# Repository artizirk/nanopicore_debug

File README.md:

# NanoPI NEO Core Debug shield

This shield provides one USB A and a uart0 via ch340 chip on seperate Micro USB connector

### Armbian Device Tree overlay for power off button on GPIO PL11

gpio-button.dts file contains the overlay. Follow [Armbian docs] to apply it.

[Armbian docs]: https://docs.armbian.com/User-Guide_Allwinner_overlays/

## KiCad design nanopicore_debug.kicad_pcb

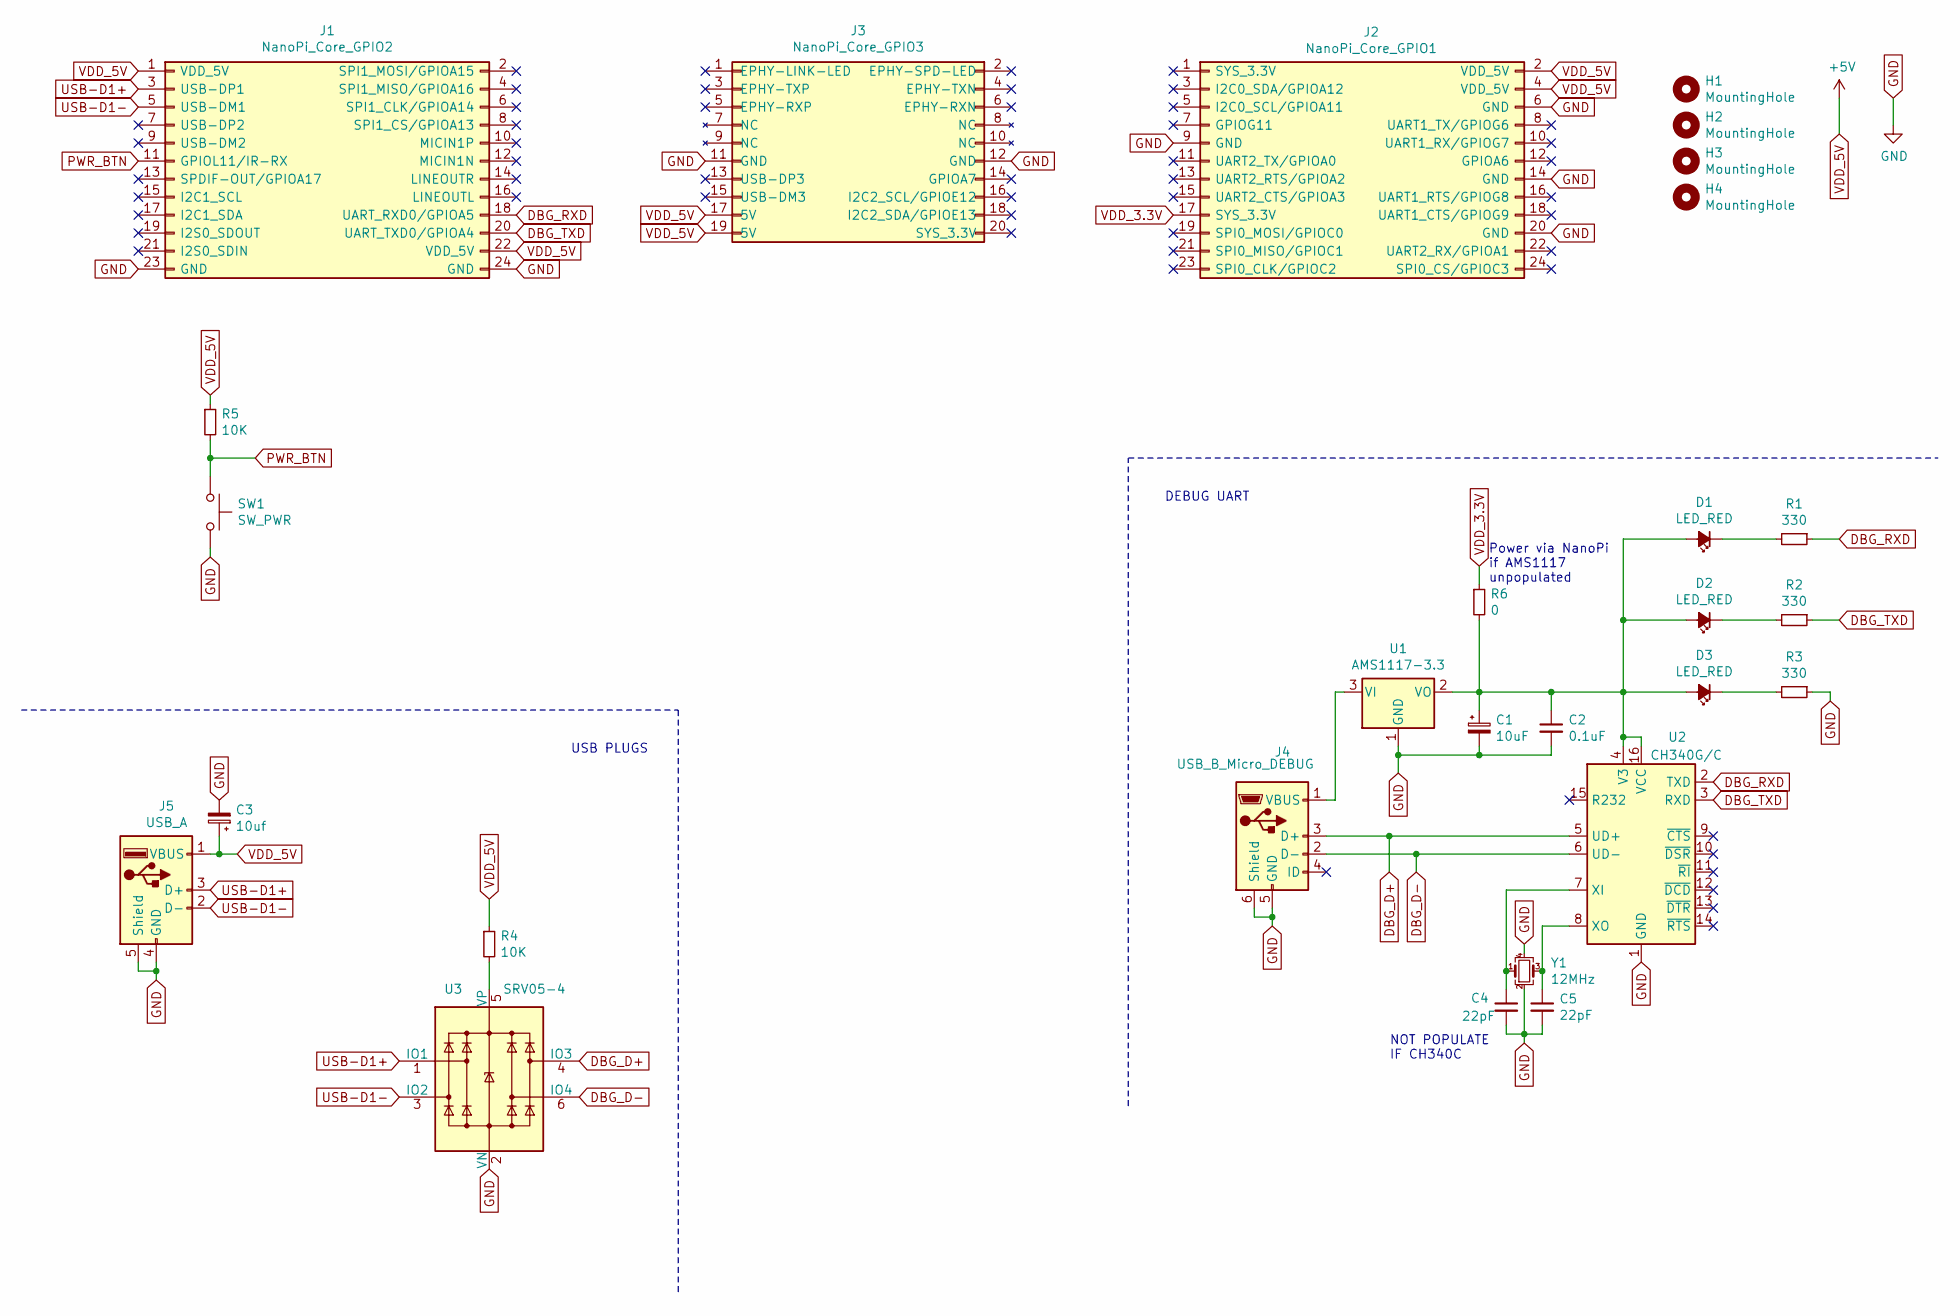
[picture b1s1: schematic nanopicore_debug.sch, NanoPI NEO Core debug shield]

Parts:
C1: 10uF; C_0805_2012Metric_Pad1.15x1.40mm_HandSolder
C2: 0.1uF; C_0805_2012Metric_Pad1.15x1.40mm_HandSolder
C3: 10uf; C_0805_2012Metric_Pad1.15x1.40mm_HandSolder
C4, C5: 22pF; C_0805_2012Metric_Pad1.15x1.40mm_HandSolder
D1, D2, D3: LED_RED; D_0805_2012Metric_Pad1.15x1.40mm_HandSolder; LCSC C84256
H1, H2, H3, H4: MountingHole; MountingHole_3mm
J1: NanoPi_Core_GPIO2; PinSocket_2x12_P2.54mm_Vertical
J2: NanoPi_Core_GPIO1; PinSocket_2x12_P2.54mm_Vertical
J3: NanoPi_Core_GPIO3; PinSocket_2x10_P2.54mm_Vertical
J4: USB_B_Micro_DEBUG; USB_Micro-B_GCT_USB3076-30-A; LCSC C393940
J5: USB_A; USB_A_Stewart_SS-52100-001_Horizontal; LCSC C2345
R1: 330; R_0805_2012Metric_Pad1.15x1.40mm_HandSolder; LCSC C17630
R2, R3: 330; R_0805_2012Metric_Pad1.15x1.40mm_HandSolder
R4, R5: 10K; R_0805_2012Metric_Pad1.15x1.40mm_HandSolder
R6: 0; R_0805_2012Metric_Pad1.15x1.40mm_HandSolder
SW1: SW_PWR; SW_SPST_TL3342; LCSC C388295
U1: AMS1117-3.3; SOT-223-3_TabPin2; LCSC C6186
U2: CH340G/C; SOIC-16_3.9x9.9mm_P1.27mm; LCSC C84681
U3: SRV05-4; SOT-23-6_Handsoldering; LCSC C85364
Y1: 12MHz; Crystal_SMD_3225-4Pin_3.2x2.5mm_HandSoldering; LCSC C9002

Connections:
DBG_D+: J4.3 (D+), U2.5 (UD+), U3.4 (IO3)
DBG_D-: J4.2 (D-), U2.6 (UD-), U3.6 (IO4)
DBG_RXD: J1.18 (UART_RXD0/GPIOA5), R1.1, U2.2 (TXD)
DBG_TXD: J1.20 (UART_TXD0/GPIOA4), R2.1, U2.3 (RXD)
GND: C1.2, C2.2, C3.2, C4.2, C5.2, J1.23 (GND), J1.24 (GND), J2.6 (GND), J2.9 (GND), J2.14 (GND), J2.20 (GND), J3.11 (GND), J3.12 (GND), J4.5 (GND), J4.6 (Shield), J5.4 (GND), J5.5 (Shield), R3.1, SW1.2, U1.1 (GND), U2.1 (GND), U3.2 (VN), Y1.2, Y1.4
unnamed: C1.1, C2.1, D1.2 (A), D2.2 (A), D3.2 (A), R6.2, U1.2 (VO), U2.4 (V3), U2.16 (VCC)
unnamed: C4.1, U2.7 (XI), Y1.1
unnamed: C5.1, U2.8 (XO), Y1.3
unnamed: D1.1 (K), R1.2
unnamed: D2.1 (K), R2.2
unnamed: D3.1 (K), R3.2
unnamed: J4.1 (VBUS), U1.3 (VI)
unnamed: R4.2, U3.5 (VP)
PWR_BTN: J1.11 (GPIOL11/IR-RX), R5.2, SW1.1
USB-D1+: J1.3 (USB-DP1), J5.3 (D+), U3.1 (IO1)
USB-D1-: J1.5 (USB-DM1), J5.2 (D-), U3.3 (IO2)
VDD_3.3V: J2.17 (SYS_3.3V), R6.1
VDD_5V: C3.1, J1.1 (VDD_5V), J1.22 (VDD_5V), J2.2 (VDD_5V), J2.4 (VDD_5V), J3.17 (5V), J3.19 (5V), J5.1 (VBUS), R4.1, R5.1

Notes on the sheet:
USB PLUGS
DEBUG UART
NOT POPULATE IF CH340C
Power via NanoPi if AMS1117 unpopulated

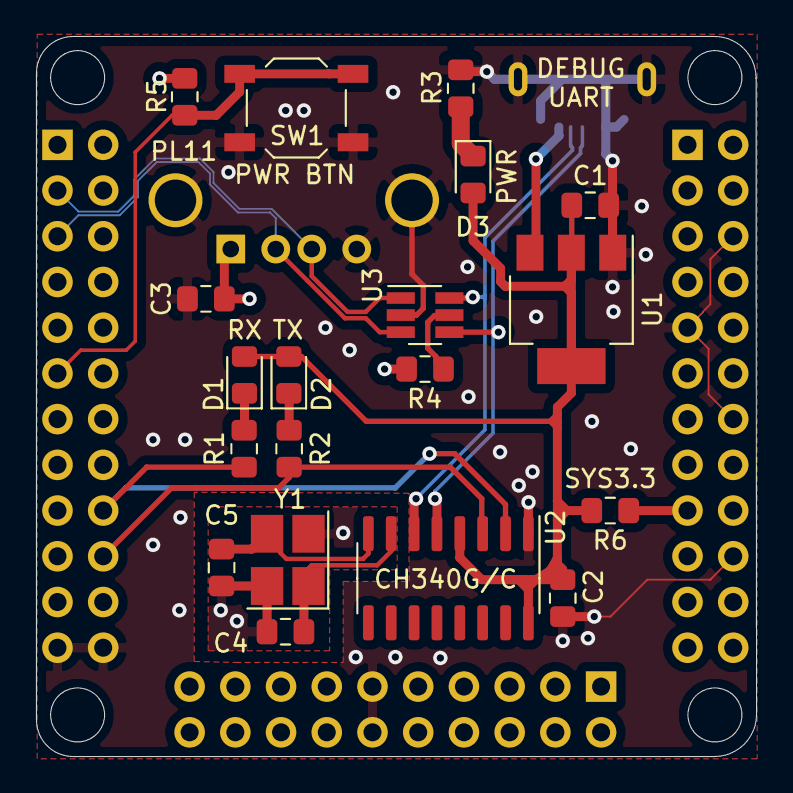
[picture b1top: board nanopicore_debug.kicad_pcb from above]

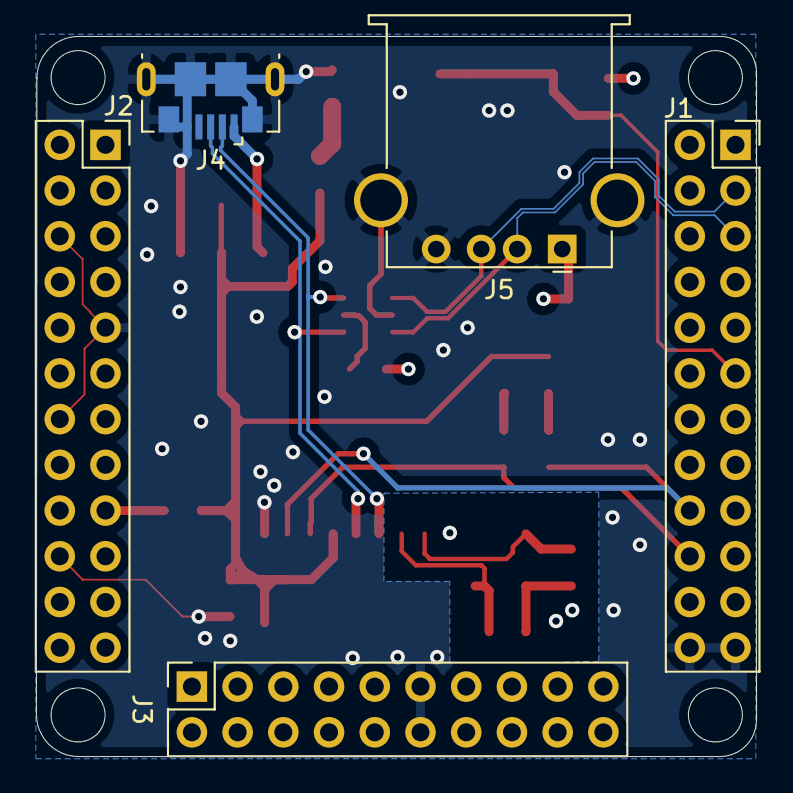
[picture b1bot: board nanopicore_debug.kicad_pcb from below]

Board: 4 copper layers, 40.0 x 40.0 mm, 28 parts (5 on the bottom side), 18 nets.

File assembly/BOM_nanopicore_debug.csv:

Id,Designator,Package,Quantity,Designation,LCSC,Link
1,U2,SOIC-16_3.9x9.9mm_P1.27mm,1,CH340G,C14267,https://lcsc.com/product-detail/USB_CH340G_C14267.html/
2,J5,USB_A_Stewart_SS-52100-001_Horizontal,1,USB_A,C2345,https://lcsc.com/product-detail/USB-Connectors_Jing-Extensio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
3,PWR,SW_SPST_TL3342,1,SW_PWR,C388295,https://lcsc.com/product-detail/Tactile-Switches_SHOU-HAN-TS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
4,"R5,R4",R_0805_2012Metric_Pad1.15x1.40mm_HandSolder,2,10K,,
5,J1,PinSocket_2x12_P2.54mm_Vertical,1,NanoPi_Core_GPIO2,,
6,J3,PinSocket_2x10_P2.54mm_Vertical,1,NanoPi_Core_GPIO3,,
7,J2,PinSocket_2x12_P2.54mm_Vertical,1,NanoPi_Core_GPIO1,,
8,"H4,H3,H2,H1",MountingHole_3mm,4,MountingHole,,
9,Y1,Crystal_SMD_3225-4Pin_3.2x2.5mm_HandSoldering,1,12MHz,C9002,https://lcsc.com/product-detail/SMD-Crystal-Resonators_Yangx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
10,U3,SOT-23-6_Handsoldering,1,SRV05-4,C85364,https://lcsc.com/product-detail/TVS_SRV05-4-P-T7_C85364.html/
11,U1,SOT-223-3_TabPin2,1,AMS1117-3.3,C6186,https://lcsc.com/product-detail/Low-Dropout-Regulators-LDO_A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
12,"R3,R2,R1",R_0805_2012Metric_Pad1.15x1.40mm_HandSolder,3,330,,
13,J4,USB_Micro-B_GCT_USB3076-30-A,1,USB_B_Micro_DEBUG,C393940,https://lcsc.com/product-detail/USB-Connectors_SHOU-HAN-MICR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
14,D3,D_0805_2012Metric_Pad1.15x1.40mm_HandSolder,1,LED_DEBUG_PWR,,
15,D2,D_0805_2012Metric_Pad1.15x1.40mm_HandSolder,1,LED_DEBUG_RXD,,
16,D1,D_0805_2012Metric_Pad1.15x1.40mm_HandSolder,1,LED_DEBUG_TXD,,
17,"C5,C4",C_0805_2012Metric_Pad1.15x1.40mm_HandSolder,2,22pF,,
18,C3,C_0805_2012Metric_Pad1.15x1.40mm_HandSolder,1,10uf,,
19,C2,C_0805_2012Metric_Pad1.15x1.40mm_HandSolder,1,0.1uF,,
20,C1,C_0805_2012Metric_Pad1.15x1.40mm_HandSolder,1,10uF,,

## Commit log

2020-04-26 init
2020-04-26 Exports and initial BOM
2020-06-21 Add 0R resistor to power CH340 from NanoPi
2020-06-22 Update BOM
2022-07-02 add device tree overlay
